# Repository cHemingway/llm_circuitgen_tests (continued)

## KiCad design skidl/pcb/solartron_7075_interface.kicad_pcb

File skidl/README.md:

# Solartron 7075 → USB interface (SKiDL)

An isolated USB interface for the Solartron 7075 DVM, described in
[SKiDL](https://github.com/devbisme/skidl) and laid out for KiCad 10. It plugs
into the 50-way Cannon socket (**SKB**) of the 7075's Parallel BCD Interface
Unit 70754 (service manual section 9). From there it reads the display data and
status lines, drives all the remote-control inputs, and connects to a host over
USB through an RP2354A.

| | |
|---|---|
| Board | 112 × 44 mm, 4 layers, 1.6 mm, rectangular, no mounting holes |
| Meter connector | J1, DD-50 **male** (plug), vertical, mounted on the **bottom** side. Two 4-40 jackscrews through its flange holes hold the board on the instrument |
| Host connector | J2, USB-B **vertical** (TE 5787834-1), mounted on the **top** side at the other end of the board |
| MCU | RP2354A (RP2350 with 2 MB of flash in the package), 12 MHz crystal, SWD header, BOOTSEL and RESET buttons |
| Isolation | 5 × TLP2361 optocouplers (4 to the meter, 1 back) + B0509S isolated DC/DC. There is a 4 mm copper-free gap between the domains (0.8 mm at the DC/DC pins) |
| Meter side | 5 × 74HCT165 (36 inputs + 4 check bits), 2 × 74HC595 (13 command outputs), supplied from its own regulated 5 V |
| Checks | SKiDL ERC: 0 errors / 0 warnings. Schematic ERC (KiCad 10, all severities): 0 violations (`pcb/erc_report.txt`). DRC with schematic parity (all severities): **0 violations, 0 unconnected, 0 parity errors** (`pcb/drc_report.txt`) |

## Schematic

One A2 sheet (`pcb/solartron_7075_interface.kicad_sch`, PDF in
`pcb/render/schematic.pdf`), grouped by function: USB input and 3.3 V, the
RP2354A, the isolation barrier (drawn as a dashed line through the
optocouplers and the DC/DC), the 595 command outputs, the meter-side 5 V, J1,
and the 165 input chain along the bottom. Labels with the same name are
connected.

SKiDL's own schematic output is not usable on this design (see
[Tool issues](#tool-issues)), so `scripts/gen_schematic.py` draws the sheet from
the SKiDL netlist. Part positions are set by hand per block; every pin then
gets a stub with a net label, power symbol or no-connect flag. The script
re-exports the netlist from the drawn sheet with `kicad-cli` and fails unless
every net has the same pins and the same name as in the SKiDL netlist.
`scripts/link_schematic.py` then ties the board's footprints to the symbols,
so KiCad's schematic-parity DRC and cross-probing work.

## How it works

```mermaid
flowchart LR
  subgraph USB["USB / host side (GND)"]
    J2[USB-B vertical] --> F1[500 mA PTC] --> ESD[USBLC6] --> LDO[AP2112K 3.3 V]
    LDO --> MCU[RP2354A]
    J2 -- D+/D- 27R --> MCU
  end
  subgraph ISO["Meter side (ISO_GND = 7075 pin 37 earth)"]
    REG[78L05] --> SR165[5 × 74HCT165]
    REG --> SR595[2 × 74HC595]
    SR595 --> Q1[2N7002 contact sample]
    SR165 --- RN[9 × 4 × 10k series]
  end
  MCU -- "SCLK, MOSI, LATCH, /OE (4 × TLP2361)" --> SR165 & SR595
  SR165 -- "MISO (1 × TLP2361)" --> MCU
  LDO -. "+5 V" .-> DCDC[B0509S 1 W isolated] -. "9 V" .-> REG
  RN --- J1[DD-50 plug to SKB]
  SR595 --- J1
  Q1 --- J1
```

* **Five signals cross the barrier.** SCLK, MOSI, LATCH and /OE go to the
  meter, and MISO comes back. Every meter output is captured by the 165 chain,
  and every meter input is driven by the 595 chain.
* **One LATCH line serves both chains.** LATCH low makes the 74HCT165s load
  (snapshot) the meter outputs. The rising edge of LATCH copies the 74HC595
  shift registers to their outputs.
* **The command outputs are safe at power-up.** The /OE optocoupler output sits
  high whenever its LED is off (MCU unpowered, in reset, or not yet
  initialised), so the 595 outputs stay high-impedance. The meter's TTL inputs
  then float to '1', which is the "nothing commanded" state. The manual notes
  that an unconnected interface leaves the meter in 10 s / DC V. The
  CONTACT-SAMPLE MOSFET has a 100 k gate pull-down for the same reason.
* **Logic levels follow the section-9 spec.**
  * Meter outputs are '1' = 2.4…6 V from a 6 kΩ source, so the 165s are
    **HCT** parts with TTL thresholds (V<sub>IH</sub> 2.0 V).
  * Each meter output passes through a 10 kΩ series resistor in a 4-way array.
    This limits ESD current and back-feeding when only one side is powered.
  * Meter inputs need '0' < 0.5 V at 5 mA sink and '1' < +5 V. The 74HC595
    meets both on a regulated 5 V.
  * That is why the meter side uses B0509S → 78L05 rather than an unregulated
    5 V → 5 V module. Such a module only holds 5 V above about 10 % load
    (20 mA), and this board draws about 15 mA, so its output would drift
    above the meter's input limit.
* **CONTACT SAMPLE** (pin 39) wants a real closure to pin 37, so it gets a
  2N7002. **PULSE SAMPLE** (pin 40) is driven directly (+5 V, keep it high for
  more than 100 µs).
* **Optocouplers.** The TLP2361 is a 15 MBd part with a totem-pole output and a
  threshold of ≤ 1.6 mA, so logic can drive its LED directly.
  * MCU side: 390 Ω from 3.3 V gives ≈ 3.6 mA.
  * Meter side: 820 Ω from 5 V gives ≈ 3.9 mA.
  * The LED cathode is pulled low by the driving logic, so each channel is
    non-inverting overall.

### RP2354A pin use

| GPIO | Pin | Function |
|---|---|---|
| GPIO20 | 32 | MISO (SPI0 RX) ← U9 |
| GPIO21 | 33 | LATCH → U7 |
| GPIO22 | 34 | SCLK (SPI0 SCK) → U5 |
| GPIO23 | 35 | MOSI (SPI0 TX) → U6 |
| GPIO24 | 36 | /OE of the 595s → U8 (drive low only after the first valid transfer) |
| GPIO5 | 8 | status LED D2 (active high) |
| SWCLK/SWDIO | 24/25 | J3 (SWCLK, GND, SWDIO) |
| QSPI_SS | 60 | BOOTSEL button SW1 (1 k) |
| RUN | 26 | RESET button SW2, 10 k pull-up |

GPIO20–24 are contiguous, so a single PIO program can drive them as well as
hardware SPI0. The QSPI pins are unconnected because the flash is inside the
RP2354A package.

## Transfer protocol and bit maps

Each transfer is 40 clocks: SPI mode 0, MSB first, SCLK ≤ 1 MHz recommended.
The optocouplers add about 0.2 µs round trip, which leaves plenty of margin
up to about 2 MHz.

1. Pulse LATCH low for ≥ 1 µs, then return it high. The pulse snapshots the
   meter outputs into the 165s. Its rising edge applies the command bytes sent
   in the previous transfer.
2. Clock 5 bytes. Read bytes 0–4 from MISO and send the command bytes on MOSI.
   Only the last two bytes sent stay in the 595 chain.
3. To apply new commands immediately, pulse LATCH again.

**MISO, bytes 0–4 (MSB first):**

| Byte | Register | bit7 … bit0 |
|---|---|---|
| 0 | U10 | 2 × 10² (16), PRINT PULSE (33), RANGE 1 (32), 1 × 10² (17), 2 × 10³ (12), RANGE 4 (30), 4 × 10² (15), 8 × 10² (14) |
| 1 | U11 | FUNC B (29), POL− (27), RANGE 2 (31), FUNC A (28), 1 × 10⁴ (9), 4 × 10³ (11), POL+ (26), 8 × 10³ (10) |
| 2 | U12 | 4 × 10⁴ (7), 2 × 10⁴ (8), 4 × 10⁰ (23), 1 × 10⁰ (25), DATA CAN CHANGE (35), 8 × 10⁴ (6), 8 × 10⁰ (22), 1 × 10¹ (21) |
| 3 | U13 | 4 × 10⁵ (3), 2 × 10¹ (20), 2 × 10⁵ (4), 4 × 10¹ (19), PRINT LEVEL (34), 8 × 10⁵ (2), 8 × 10¹ (18), 1 × 10⁶ (1) |
| 4 | U14 | 1 × 10⁵ (5), 1 × 10³ (13), OVERLOAD (36), 2 × 10⁰ (24), **1**, **0**, **1**, **0** |

Bits 3–0 of byte 4 are wired to a fixed `1010` pattern on the meter side.
If they read back as anything else, the link is broken or the isolated side is
unpowered: an unpowered side reads as all ones.

The bits don't follow the connector order, and a decade's four bits can be
split across registers. Each signal uses whichever array channel and register
input is nearest its connector pin (see [Routing review](#routing-review)).
Firmware should decode them with these tables, which are also printed on the
schematic.

**MOSI, bytes 3 and 4 (the last two sent):**

| Byte | Register | bit7 (QH) … bit0 (QA) |
|---|---|---|
| 3 | U16 | –, –, FRONT PANEL LOCKOUT (38, 0 = lockout/remote), FUNC (43), PULSE SAMPLE (40), FUNC (42), RATIO (41, 0 = ratio), CONTACT SAMPLE (39, via Q1, 1 = close) |
| 4 | U15 | REMOTE LED D4, RANGE 4 (50), RANGE 2 (49), RANGE 1 (48), INTEG 2 (45), AUTORANGE inhibit (47), INTEG 1 (46), INTEG 4 (44) |

Bytes 0–2 on MOSI are don't-care: they fall out of the end of the 595 chain.

Typical remote measurement:

1. Write the function, range and integration codes from the manual's tables,
   with LOCKOUT = 0.
2. Set PULSE SAMPLE = 1, wait ≥ 100 µs, then set it back to 0. Each change
   is one transfer plus a LATCH pulse.
3. Poll until PRINT LEVEL = 1.
4. Read the BCD digits, polarity, range and function codes from the same
   snapshot.

## Connector pin map (J1 ↔ 70754 SKB)

| SKB pin | Signal | Board net | SKB pin | Signal | Board net |
|---|---|---|---|---|---|
| 1 | 1 × 10⁶ | BCD_1E6_1 | 26 / 27 | +ve / −ve polarity | POL_POS / POL_NEG |
| 2–5 | 8,4,2,1 × 10⁵ | BCD_1E5_* | 28 / 29 | function out | FUNC_OUT_A / B |
| 6–9 | × 10⁴ | BCD_1E4_* | 30 / 31 / 32 | range out (4/2/1) | RANGE_OUT_* |
| 10–13 | × 10³ | BCD_1E3_* | 33 / 34 | print pulse / level | PRINT_PULSE / PRINT_LEVEL |
| 14–17 | × 10² | BCD_1E2_* | 35 / 36 | data can change / overload | DATA_CAN_CHANGE / OVERLOAD |
| 18–21 | × 10¹ | BCD_1E1_* | 37 | earth / logic 0 | **ISO_GND** (+ J1 shell) |
| 22–25 | × 10⁰ | BCD_1E0_* | 38–50 | command inputs | see MOSI map |

## Mechanical notes

* **J1 is on the underside**, centred at (36, 22) mm in the KiCad top view.
  * Its pins 1–17 (the wide row of the D) face the board's lower edge, the edge
    with the "ISOLATED (METER EARTH)" legend.
  * The jackscrew holes are Ø 3.2 mm at (5.445, 22) and (66.555, 22), 61.11 mm
    apart (DD-50 standard).
  * Fit two 4-40 UNC jackscrews or thumbscrews from the top through the board
    and the connector flange into the socket's screw-locks. Thread length should
    be ≥ 10 mm (1.6 mm board + flange + engagement).
  * No other parts sit on the underside. Keep at least 3 mm of clearance around
    the screw heads on top, which the layout already does.
* The board stands off the instrument by roughly the connector's body height,
  about 12 mm for the Amphenol Delta-D straight series. Check this against the
  part you buy.
* Relative to the socket, the board extends 36 mm on the J1 side and 76 mm on
  the USB side. If something on your unit is in the way on that side, J1's
  orientation can be changed in `scripts/layout_pcb.py` (`j1_ok`). Everything
  else then needs re-placing.
* The vertical USB-B on the top face points away from the instrument.

## Parts and sourcing

* Every part has an LCSC code. The grouped BOM with MPNs is in
  `output/bom.csv`, and the JLCPCB-format BOM and CPL are in `pcb/fab/`.
* Symbols and footprints come from the stock KiCad 10 libraries, except:
  * **J1:** KiCad 10 has no 50-way D-sub. `scripts/gen_dd50_footprint.py` and
    `scripts/gen_symbols.py` generate `lib/Solartron7075.*` from the Amphenol
    Delta-D drawing.
  * **TLP2361:** there is no KiCad symbol, so the identically-pinned
    `Isolator:TLP2310` symbol is used (SO6 with 5 leads: A 1, K 3, GND 4, VO 5,
    VCC 6). The footprint is `Toshiba_SOIC-5-6`.
  * **B0509S-1WR3:** uses the Murata MEE1 symbol and footprint, which have the
    same SIP-4 pinout.
* **J1 (Amphenol D50P24A4PA00LF, C17502305)** was listed on LCSC without stock
  at design time. Any straight-PCB DD-50 plug with plain 3.1 mm flange holes on
  the standard 2.77 × 2.84 mm grid fits. Don't use one with female screw-locks.
* The jackscrews are not on LCSC.
* Power budget is under 120 mA from USB:
  * RP2354A: ~30 mA
  * Opto LEDs: ≤ 15 mA
  * LEDs: ~5 mA
  * Isolated side: ≈ 15 mA at 5 V, ≈ 40 mA at the DC/DC input
* Isolation is **functional**: its purpose is to break the USB/earth ground loop
  and keep USB noise away from the meter. It is not a safety barrier. The
  TLP2361s are rated 3.75 kV<sub>rms</sub> and the B0509S 1.5 kV DC.

## Routing review

After review, the meter-side wiring was tidied in two rounds. J1, the
resistor arrays, the optocouplers and everything on the host side stayed
where they were.

1. **Pin swaps within parts** (`scripts/optimise_pins.py`). Every signal
   stayed on its original register and array. Only the pin it used there
   changed: the 74HCT165 D inputs, the array channels and the 74HC595
   outputs.
2. **Pin swaps between parts, and moved registers**
   (`scripts/optimise_layout.py`):
   * Any meter output may now use any array channel and any 74HCT165 input,
     so each signal takes the one nearest its connector pin. The four spare
     inputs become the link-check bits.
   * Any command input may use any 74HC595 output.
   * All seven registers are turned 180°, so their clock, latch and supply
     pins face away from J1 and the arrays. Their decoupling capacitors moved
     with the supply pins.
   * The 74HCT165s are reordered along the bottom row into chain order (U13,
     U12, U11, U10 from left to right), which puts U10 next to the MISO
     optocoupler. U15 and U16 swapped places.

Both scripts read the pad positions from the board. They use simulated
annealing to minimise the crossings of the straight pad-to-pad lines, plus
their length. The second round also counts the clock, latch, /OE, MOSI and
chain nets, so moving a register is weighed against its control wiring. The
result is in the `ARRAYS`, `REGS_165` and `REGS_595` tables in
`solartron_7075_interface.py` and the `BOTTOM_ROW` and `TOP_ROW` tables in
`scripts/layout_pcb.py`. Each round was re-routed with Freerouting.
`scripts/routing_metrics.py` measures the boards (original → round 1 → round
2):

| Nets | Straight-line crossings | Track length (mm) | Vias |
|---|---|---|---|
| J1 → resistor arrays (36) | 148 → 102 → **10** | 513 → 481 → **255** | 21 → 18 → **6** |
| Resistor arrays → 74HCT165s (36) | 64 → 0 → **0** | 441 → 351 → **372** | 72 → 70 → **72** |
| 74HC595s → J1 (13) | 36 → 8 → **1** | 265 → 205 → **137** | 11 → 11 → **7** |
| Clock, latch, /OE, MOSI, chains (10) | | 563 → 558 → **494** | 16 → 21 → **20** |
| Whole board | | 2428 → 2227 → **1868** | 262 → 260 → **243** |

DRC, ERC and the schematic-parity check are clean after each round.

The array-to-register links still drop to the bottom layer, at two vias
each, because of the 74HCT165 pinout. Its D inputs are rows 3–6 of each pin
column, behind Q7, DS, GND and ~Q7. Reaching them from above on the top layer
would need eight tracks between the pin columns, and they don't fit. On the
bottom layer the links are short, straight and parallel.

## Gerbers and prints

| File | Contents |
|---|---|
| `pcb/fab/gerbers.zip` | Gerbers for 4 layers, mask, paste, silkscreen and outline, plus Excellon drill files (PTH; the NPTH file is empty) and drill maps. Upload this to the board house |
| `pcb/fab/bom_jlcpcb.csv`, `pcb/fab/cpl_jlcpcb.csv` | JLCPCB assembly BOM and placement |
| `pcb/print/pcb_prints.pdf` | 7 A4 pages, black and white, with title block: top and bottom assembly (fab layers, pads sketched), F.Cu, In1.Cu, In2.Cu and B.Cu, all at 2:1, then a 1:1 bottom view for a fit check |
| `pcb/print/gerber_preview.png` | the Gerber and drill files rendered by gerbv, independently of KiCad |
| `pcb/render/` | KiCad 3D renders and a colour multi-layer PDF |

For the fit check, print page 7 at 100 % ("actual size"). The board outline
there should measure 112 × 44 mm. Hold it against the meter's SKB socket to
check the jackscrew holes, the pin rows and the overhang on each side. Bottom
views (pages 2, 6 and 7) are mirrored, so they show the board as seen from
the meter side.

## Files

| Path | What |
|---|---|
| `solartron_7075_interface.py` | the SKiDL design (all parts, nets, LCSC/MPN fields) |
| `lib/` | generated DD-50 symbol + footprint |
| `scripts/gen_dd50_footprint.py`, `scripts/gen_symbols.py` | library generators |
| `scripts/layout_pcb.py` | placement, stack-up, rules, planes, isolation keep-outs, silkscreen |
| `scripts/route_pcb.py`, `scripts/fanout.py` | QFN hand fan-out, plane vias, Freerouting, clean-up, ground pours |
| `scripts/gen_schematic.py` | draws the single-page schematic from the netlist and checks it (`--check`) |
| `scripts/link_schematic.py` | links the routed board to the schematic (symbol paths, net names) |
| `scripts/make_bom.py`, `scripts/jlc_cpl.py` | BOM and placement files |
| `scripts/optimise_pins.py`, `scripts/optimise_layout.py`, `scripts/routing_metrics.py` | meter-side pin-swap and register-placement searches, and the routing figures used to compare boards |
| `scripts/make_prints.py` | the print PDF and the Gerber preview |
| `build.sh` | runs the whole flow |
| `CONVERSATION.md` | export of the Claude Code session that produced this design, with its time and token totals |
| `REVIEW_CONVERSATION.md` | the review part of the same session (pin swaps and moved registers), with its statistics |
| `scripts/session_breakdown.py`, `stats/breakdown_calls.csv` | the split of the design session's statistics by kind of work, and the category of every API call |
| `scripts/review_breakdown.py`, `stats/review_breakdown_calls.csv` | the same for the review |
| `output/` | SKiDL netlist, ERC log, BOM, unplaced board straight from SKiDL |
| `pcb/` | KiCad 10 project: schematic, routed board, ERC and DRC reports, `render/` (schematic PDF/PNG, board renders), `print/` (prints, Gerber preview), `fab/` (Gerbers, drill, BOM, CPL) |

## Rebuilding

Tested with KiCad 10.0.6 (Ubuntu PPA), SKiDL 2.3.0 with kinet2pcb 1.1.4,
Freerouting 2.5.0 (needs Java 25), and Python 3.12. Use the system Python,
because it has KiCad's `pcbnew` module. The prints need `pdfunite` and
`pdftoppm` (poppler-utils) and ImageMagick. `gerbv` is optional; without it the
Gerber preview is skipped.

```sh
python3 -m venv --system-site-packages .venv && .venv/bin/pip install skidl
SKIDL_PYTHON=.venv/bin/python FREEROUTING_JAR=/path/freerouting-2.5.0-executable.jar \
JAVA=/usr/lib/jvm/java-25-openjdk-amd64/bin/java ./build.sh
```

The full run takes about 8 minutes, mostly in Freerouting's optimiser.
Freerouting is not fully deterministic, so a rebuild gives a board that is
equivalent but not byte-identical. The committed board is the one checked by
`pcb/drc_report.txt`.

## Session statistics breakdown

The root README's Breakdown table for SKiDL comes from
`scripts/session_breakdown.py`, which reads the session's Claude Code
transcript. The category of each of the 347 API calls is listed in
`stats/breakdown_calls.csv`. Notes on the method:

* **Span.** The span runs from the first prompt to the request to export the
  conversation, the same as the Results row. This session has not had the
  review comments yet.
* **Categories.** Calls are assigned by hand, from index ranges in the script.
  The less obvious calls:
  * Installing KiCad and SKiDL counts as tool research. Freerouting, Java and
    the 3D models count as PCB.
  * Checking which footprints fit the chosen parts counts as PCB, and so does
    the DD-50 footprint.
  * The BOM and the later LED and passive swaps count as part selection.
  * Linking the board to the schematic (`link_schematic.py`, the parity DRC)
    counts as PCB.
* **Cache rewrite.** "Other" includes a 0.62 M-token prompt-cache write
  (about $5). The first call after the 6 h pause at the usage limit had to
  re-cache the whole conversation, and that call was a `git status` check.
* **Not attributable.** This column holds the automatic compaction (77 s) and
  1.13 M tokens that the cost counter includes but the transcript does not log
  per call.
* **Prices.** The fitted prices are $4.41 per million input tokens, $8.00 for
  cache writes, $0.200 for cache reads and $20.03 for output.
  * They reproduce all four of the session's cost snapshots to within 1e-13
    dollars.
  * Four snapshots and four prices make the fit exact. So it is checked only
    by the other three prices coming out as round figures.
  * The input price is poorly determined, because there are only 5 k uncached
    input tokens. Its effect on any column is under $0.02.
  * Snapshots written later in the session (nine in all) refit the input price
    to $3.90. Re-running the script then gives $7.52 for "Other" instead of
    the published $7.51.

## Tool issues

Problems with SKiDL, kinet2pcb, Freerouting and the KiCad libraries, and what
this flow does about them.

* **SKiDL schematic generator.** SKiDL 2.3's KiCad 10 schematic output
  (`SKIDL_SCH=1`, hierarchical or flat) runs, but on this design it draws some
  power symbols and labels touching other nets. KiCad's netlist export of the
  result merges nets, e.g. +3V3 with +1V1_DVDD, and puts decoupling caps on the
  wrong rails. It is off by default. The shipped sheet comes from
  `scripts/gen_schematic.py` and is checked against the netlist, as described
  under [Schematic](#schematic).
* **kinet2pcb:**
  * It can't parse KiCad 10's quoted `fp-lib-table` entries, so the footprint
    directories are passed explicitly.
  * It puts every no-connect pin on one shared `__NOCONNECT` net, so
    `layout_pcb.py` detaches them.
  * Its footprints carry no symbol paths, so the board is not linked to any
    schematic. `link_schematic.py` adds the paths and BOM fields, renames nets
    the way KiCad's "Update PCB from Schematic" would (local-label nets become
    `/NAME`), and gives no-connect pins their `unconnected-(…)` nets.
* **SKiDL pin names.** SKiDL mangles pin names containing `'` (the 595's
  `QH'`), so pin numbers are used there.
* **Freerouting** doesn't drop vias into the inner planes by itself, and it
  can't escape the RP2354A's 0.4 mm-pitch supply pins. The QFN fan-out and the
  plane vias are pre-routed and locked, and Freerouting routes the rest. It is
  also not fully deterministic (see [Rebuilding](#rebuilding)).
* **KiCad libraries.** There is no 50-way D-sub footprint or TLP2361 symbol,
  so these are generated or substituted (see
  [Parts and sourcing](#parts-and-sourcing)). The 3D library has no models for
  the DD-50, the vertical USB-B, the TS-1187A switches, the MEE1/B0509S or the
  QFN-60, so those parts are missing from the renders.

## Design caveats

* **Not built or bench-tested.** Before ordering:
  * Check J1's footprint against the datasheet of the plug you actually buy.
  * Check the jackscrew thread and the socket orientation on your 70754.
  * Check the orientation of every part in JLCPCB's placement preview.
* **Power sequencing.** If the meter is switched off while the board is powered
  and /OE is enabled, the 595 outputs back-feed the meter's TTL inputs.
  Firmware should release /OE when the meter outputs read implausibly, for
  example everything low.
* The 595s' '1' level is the 78L05 output, 5.0 V ± 4 %. The manual gives
  "< +5 V" for its inputs, which the TTL inputs tolerate.
* J1 had no LCSC stock at design time, and the jackscrews are not on LCSC (see
  [Parts and sourcing](#parts-and-sourcing)).
* Isolation is functional, not a safety barrier.
* No firmware is included.

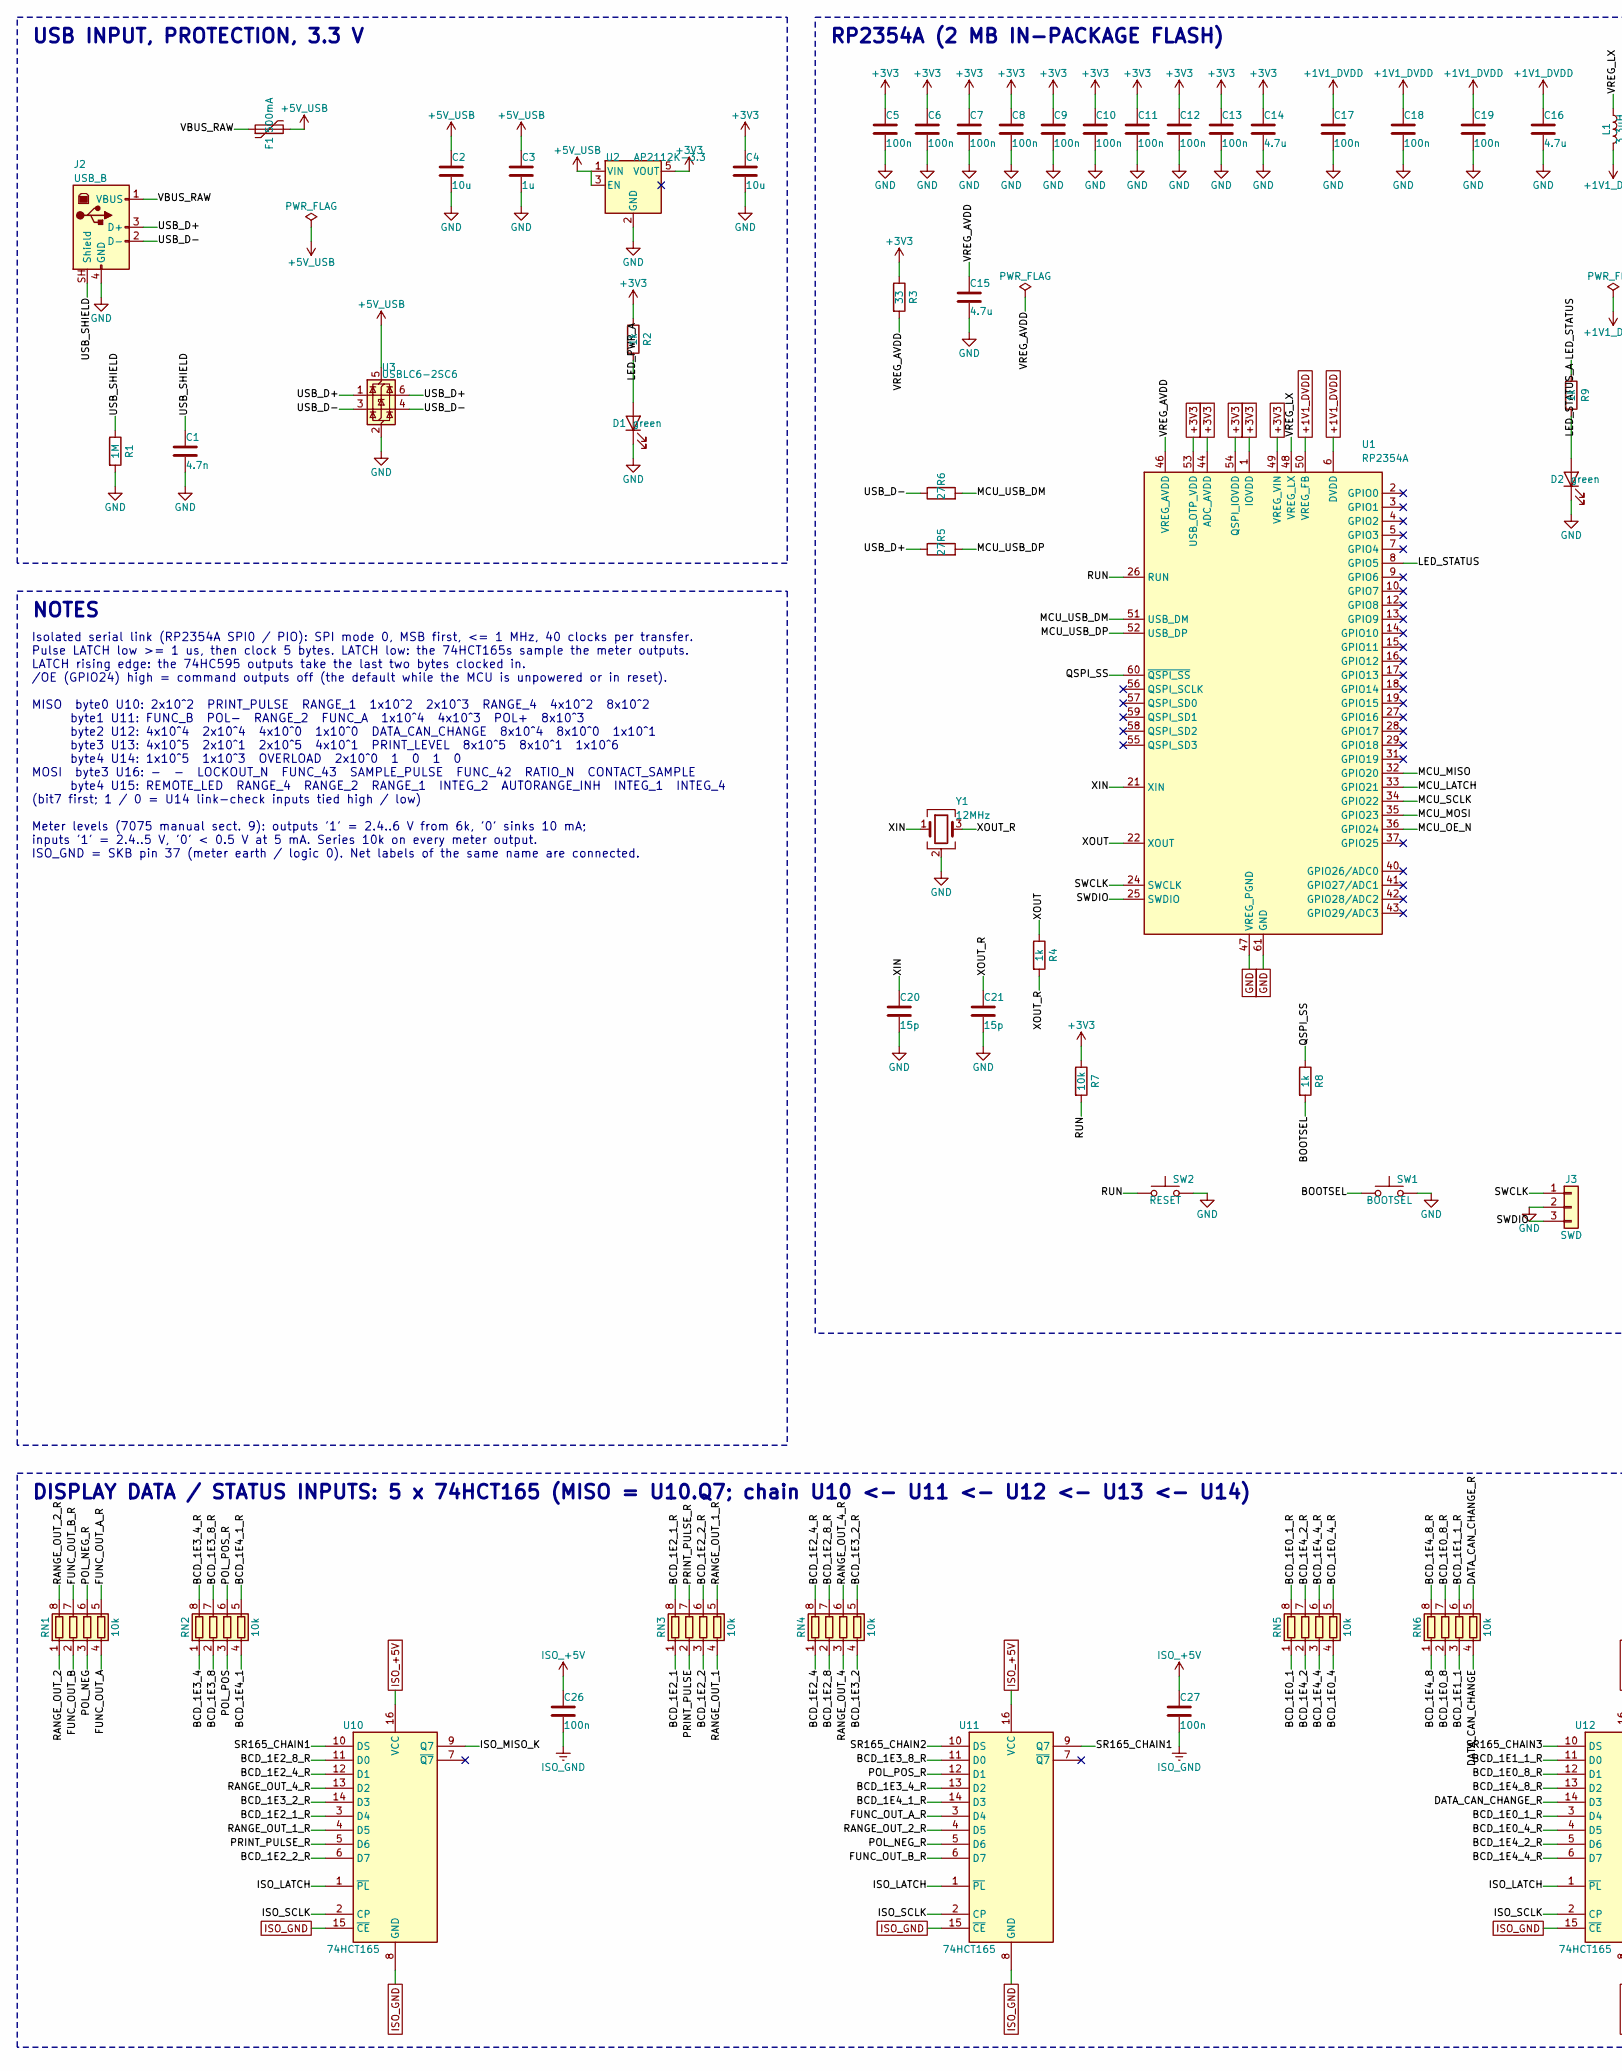
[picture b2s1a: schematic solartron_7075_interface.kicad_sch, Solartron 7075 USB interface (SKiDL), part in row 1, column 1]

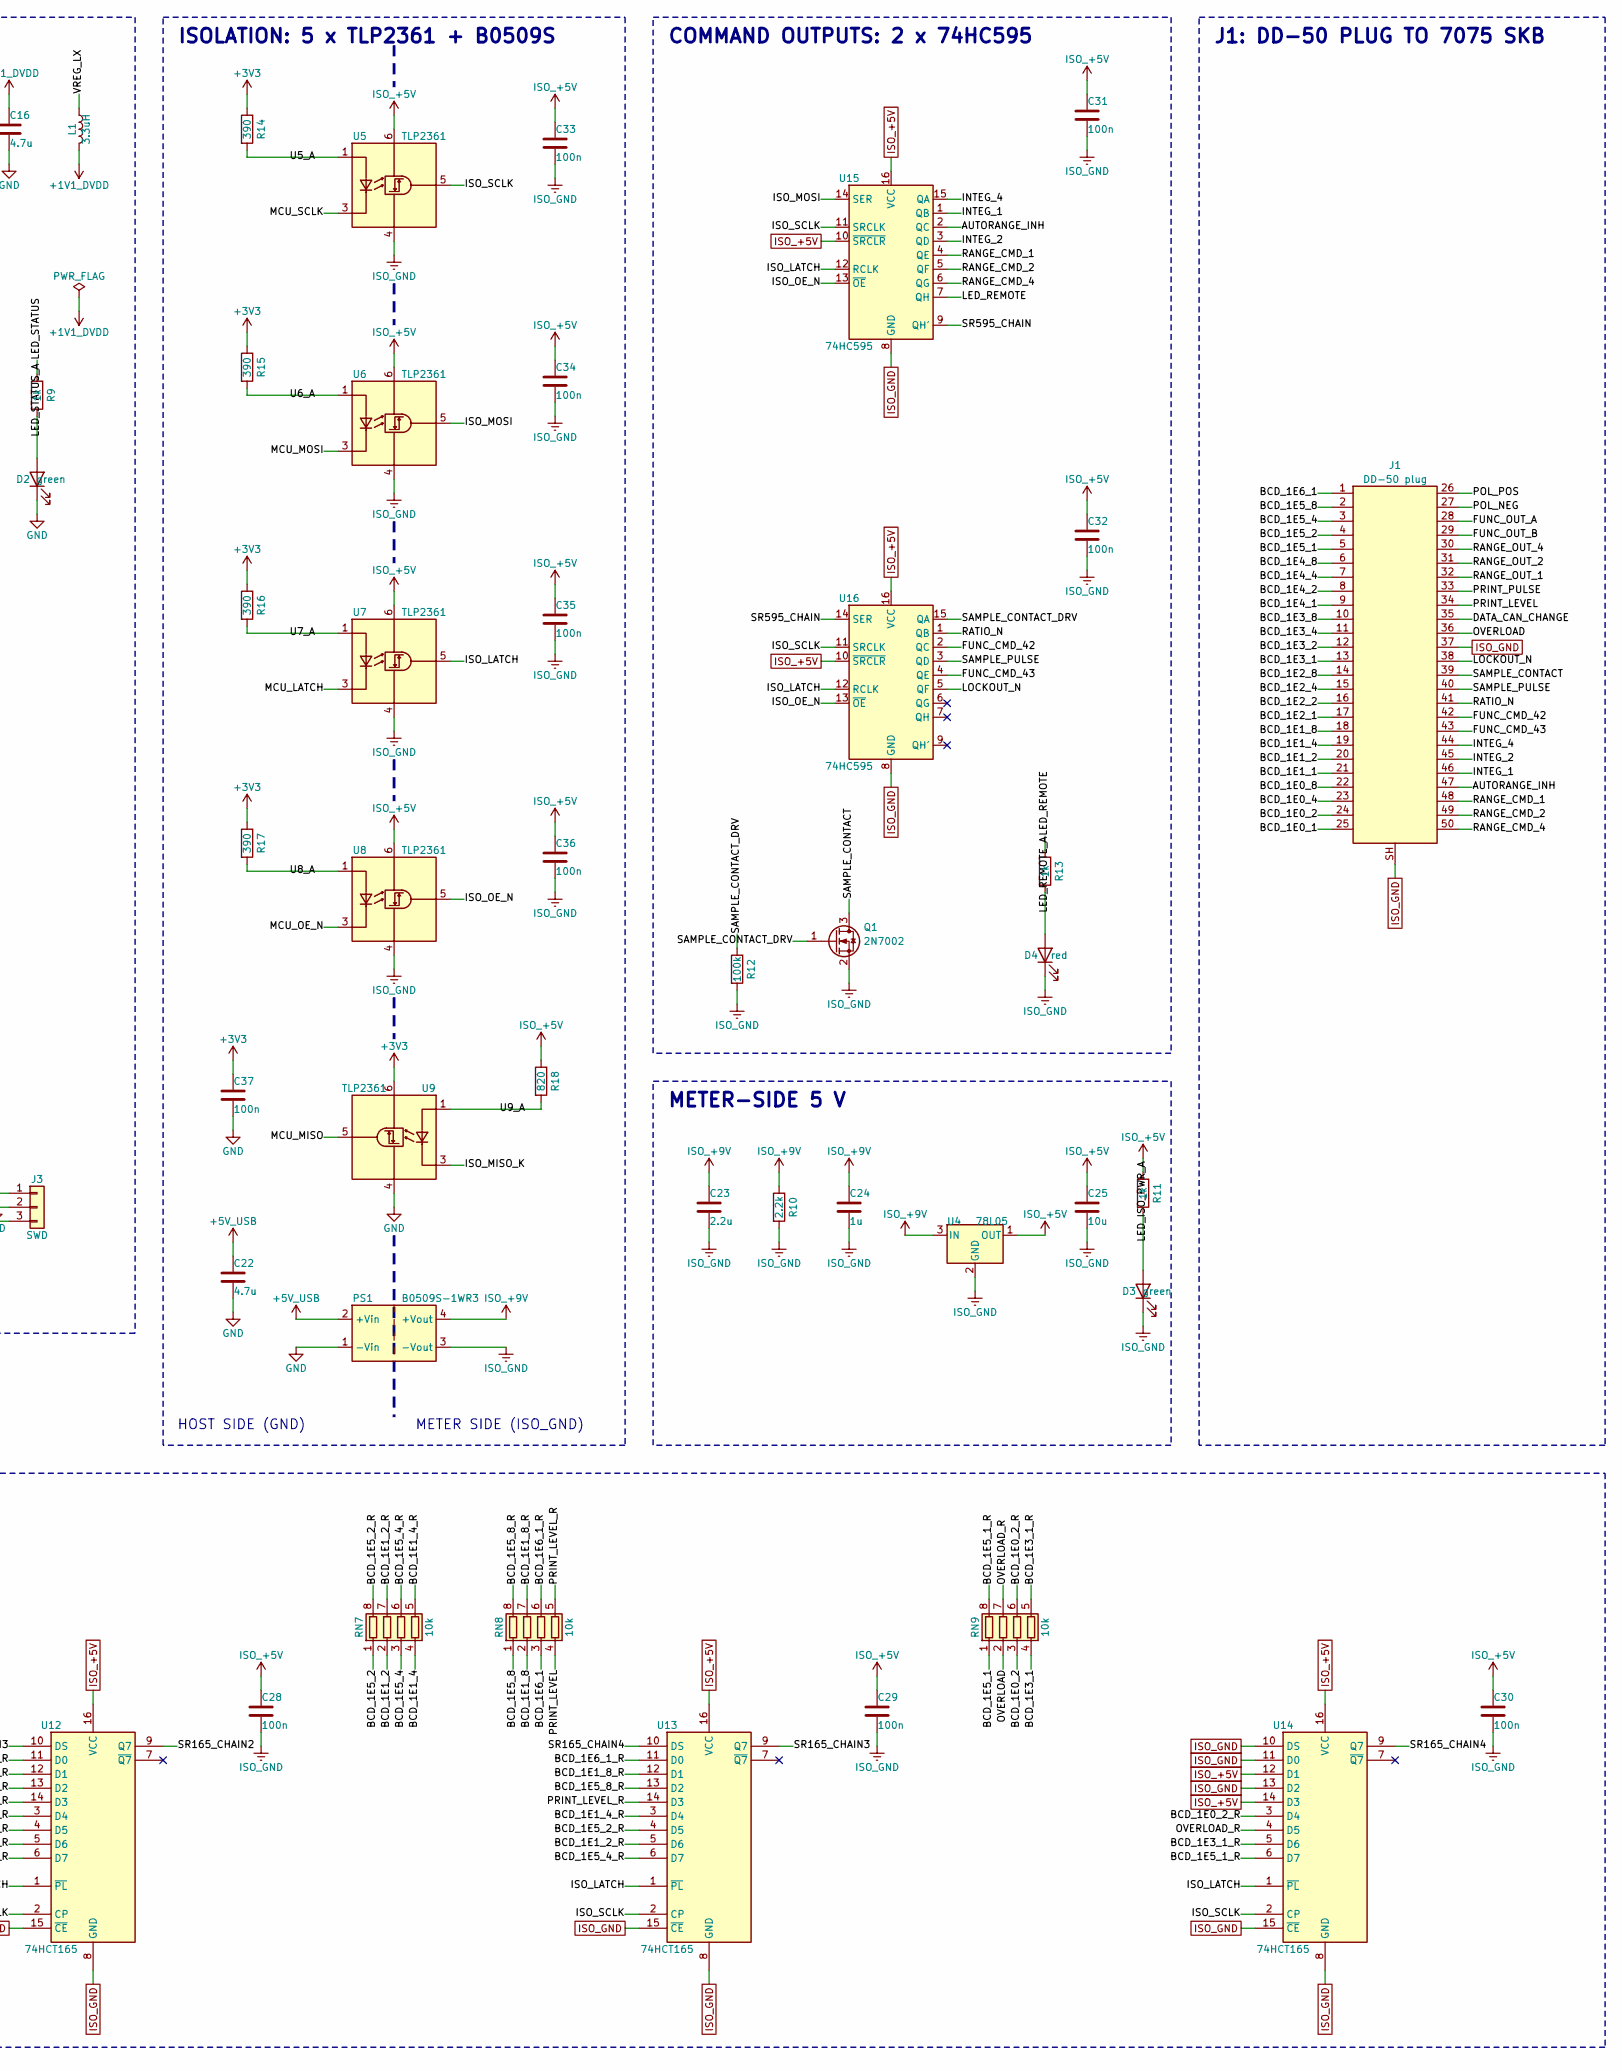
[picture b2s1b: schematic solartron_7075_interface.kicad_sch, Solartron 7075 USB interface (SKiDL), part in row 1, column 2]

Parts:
C1: 4.7n; C_0603_1608Metric; MPN 0603B472K500NT; LCSC C53987
C2, C4, C25: 10u; C_0603_1608Metric; MPN CL10A106KP8NNNC; LCSC C19702
C3, C24: 1u; C_0603_1608Metric; MPN CL10A105KB8NNNC; LCSC C15849
C5, C6, C7, C8, C9, C10, C11, C12, C13, C17, C18, C19: 100n; C_0402_1005Metric; MPN CL05B104KO5NNNC; LCSC C1525
C14, C15, C16: 4.7u; C_0402_1005Metric; MPN CL05A475MP5NRNC; LCSC C23733
C20, C21: 15p; C_0402_1005Metric; MPN 0402CG150J500NT; LCSC C1548
C22: 4.7u; C_0603_1608Metric; MPN CL10A475KO8NNNC; LCSC C19666
C23: 2.2u; C_0603_1608Metric; MPN CL10A225KO8NNNC; LCSC C23630
C26, C27, C28, C29, C30, C31, C32, C33, C34, C35, C36, C37: 100n; C_0603_1608Metric; MPN CC0603KRX7R9BB104; LCSC C14663
D1, D2, D3: green; LED_0603_1608Metric; MPN LTST-C190KGKT; LCSC C125094
D4: red; LED_0603_1608Metric; MPN KT-0603R; LCSC C2286
F1: 500mA; Fuse_1206_3216Metric; MPN SMD1206P050TF; LCSC C20799
J1: DD-50 plug; DSUB-50_Pins_Vertical_P2.77x2.84mm_MountingHoles; MPN D50P24A4PA00LF; LCSC C17502305
J2: USB_B; USB_B_TE_5787834_Vertical; MPN 5787834-1; LCSC C592900
J3: SWD; PinHeader_1x03_P2.54mm_Vertical; MPN PZ254V-11-03P; LCSC C2937625
L1: 3.3uH; L_Murata_DFE201610P; MPN AOTA-B201610S3R3-101-T; LCSC C42411119
PS1: B0509S-1WR3; Converter_DCDC_Murata_MEE1SxxxxSC_THT; MPN B0509S-1WR3; LCSC C7500906
Q1: 2N7002; SOT-23; MPN 2N7002; LCSC C8545
R1: 1M; R_0603_1608Metric; MPN 0603WAF1004T5E; LCSC C22935
R2, R11, R13: 1k; R_0603_1608Metric; MPN 0603WAF1001T5E; LCSC C21190
R3: 33; R_0402_1005Metric; MPN 0402WGF330JTCE; LCSC C25105
R4, R8, R9: 1k; R_0402_1005Metric; MPN 0402WGF1001TCE; LCSC C11702
R5, R6: 27; R_0402_1005Metric; MPN 0402WGF270JTCE; LCSC C25100
R7: 10k; R_0402_1005Metric; MPN 0402WGF1002TCE; LCSC C25744
R10: 2.2k; R_0603_1608Metric; MPN 0603WAF2201T5E; LCSC C4190
R12: 100k; R_0603_1608Metric; MPN 0603WAF1003T5E; LCSC C25803
R14, R15, R16, R17: 390; R_0603_1608Metric; MPN 0603WAF3900T5E; LCSC C23151
R18: 820; R_0603_1608Metric; MPN 0603WAF8200T5E; LCSC C23253
RN1, RN2, RN3, RN4, RN5, RN6, RN7, RN8, RN9: 10k; R_Array_Convex_4x0603; MPN 4D03WGJ0103T5E; LCSC C29718
SW1: BOOTSEL; SW_Push_1P1T_XKB_TS-1187A; MPN TS-1187A-B-A-B; LCSC C318884
SW2: RESET; SW_Push_1P1T_XKB_TS-1187A; MPN TS-1187A-B-A-B; LCSC C318884
U1: RP2354A; QFN-60-1EP_7x7mm_P0.4mm_EP3.4x3.4mm_ThermalVias; MPN RP2354A; LCSC C41378174
U2: AP2112K-3.3; SOT-23-5; MPN AP2112K-3.3TRG1; LCSC C51118
U3: USBLC6-2SC6; SOT-23-6; MPN USBLC6-2SC6; LCSC C7519
U4: 78L05; SOT-89-3; MPN 78L05 (SOT-89); LCSC C347258
U5, U6, U7, U8, U9: TLP2361; Toshiba_SOIC-5-6_4.4x3.6mm_P1.27mm; MPN TLP2361(TPL,E; LCSC C107626
U10, U11, U12, U13, U14: 74HCT165; SOIC-16_3.9x9.9mm_P1.27mm; MPN 74HCT165D,653; LCSC C456131
U15, U16: 74HC595; SOIC-16_3.9x9.9mm_P1.27mm; MPN 74HC595D,118; LCSC C5947
Y1: 12MHz; Crystal_SMD_3225-4Pin_3.2x2.5mm; MPN ABM8-272-T3; LCSC C20625731

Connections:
+1V1_DVDD: C16.1, C17.1, C18.1, C19.1, L1.2, U1.6 (DVDD), U1.23 (DVDD), U1.39 (DVDD), U1.50 (VREG_FB)
+3V3: C4.1, C5.1, C6.1, C7.1, C8.1, C9.1, C10.1, C11.1, C12.1, C13.1, C14.1, C37.1, R2.1, R3.1, R7.1, R14.1, R15.1, R16.1, R17.1, U1.1 (IOVDD), U1.11 (IOVDD), U1.20 (IOVDD), U1.30 (IOVDD), U1.38 (IOVDD), U1.44 (ADC_AVDD), U1.45 (IOVDD), U1.49 (VREG_VIN), U1.53 (USB_OTP_VDD), U1.54 (QSPI_IOVDD), U2.5 (VOUT), U9.6 (VDD)
+5V_USB: C2.1, C3.1, C22.1, F1.2, PS1.2 (+Vin), U2.1 (VIN), U2.3 (EN), U3.5 (VBUS)
/AUTORANGE_INH: J1.47, U15.2 (QC)
/BCD_1E0_1: J1.25, RN5.1 (R1.1)
/BCD_1E0_1_R: RN5.8 (R1.2), U12.3 (D4)
/BCD_1E0_2: J1.24, RN9.3 (R3.1)
/BCD_1E0_2_R: RN9.6 (R3.2), U14.3 (D4)
/BCD_1E0_4: J1.23, RN5.4 (R4.1)
/BCD_1E0_4_R: RN5.5 (R4.2), U12.4 (D5)
/BCD_1E0_8: J1.22, RN6.2 (R2.1)
/BCD_1E0_8_R: RN6.7 (R2.2), U12.12 (D1)
/BCD_1E1_1: J1.21, RN6.3 (R3.1)
/BCD_1E1_1_R: RN6.6 (R3.2), U12.11 (D0)
/BCD_1E1_2: J1.20, RN7.2 (R2.1)
/BCD_1E1_2_R: RN7.7 (R2.2), U13.5 (D6)
/BCD_1E1_4: J1.19, RN7.4 (R4.1)
/BCD_1E1_4_R: RN7.5 (R4.2), U13.3 (D4)
/BCD_1E1_8: J1.18, RN8.2 (R2.1)
/BCD_1E1_8_R: RN8.7 (R2.2), U13.12 (D1)
/BCD_1E2_1: J1.17, RN3.1 (R1.1)
/BCD_1E2_1_R: RN3.8 (R1.2), U10.3 (D4)
/BCD_1E2_2: J1.16, RN3.3 (R3.1)
/BCD_1E2_2_R: RN3.6 (R3.2), U10.6 (D7)
/BCD_1E2_4: J1.15, RN4.1 (R1.1)
/BCD_1E2_4_R: RN4.8 (R1.2), U10.12 (D1)
/BCD_1E2_8: J1.14, RN4.2 (R2.1)
/BCD_1E2_8_R: RN4.7 (R2.2), U10.11 (D0)
/BCD_1E3_1: J1.13, RN9.4 (R4.1)
/BCD_1E3_1_R: RN9.5 (R4.2), U14.5 (D6)
/BCD_1E3_2: J1.12, RN4.4 (R4.1)
/BCD_1E3_2_R: RN4.5 (R4.2), U10.14 (D3)
/BCD_1E3_4: J1.11, RN2.1 (R1.1)
/BCD_1E3_4_R: RN2.8 (R1.2), U11.13 (D2)
/BCD_1E3_8: J1.10, RN2.2 (R2.1)
/BCD_1E3_8_R: RN2.7 (R2.2), U11.11 (D0)
/BCD_1E4_1: J1.9, RN2.4 (R4.1)
/BCD_1E4_1_R: RN2.5 (R4.2), U11.14 (D3)
/BCD_1E4_2: J1.8, RN5.2 (R2.1)
/BCD_1E4_2_R: RN5.7 (R2.2), U12.5 (D6)
/BCD_1E4_4: J1.7, RN5.3 (R3.1)
/BCD_1E4_4_R: RN5.6 (R3.2), U12.6 (D7)
/BCD_1E4_8: J1.6, RN6.1 (R1.1)
/BCD_1E4_8_R: RN6.8 (R1.2), U12.13 (D2)
/BCD_1E5_1: J1.5, RN9.1 (R1.1)
/BCD_1E5_1_R: RN9.8 (R1.2), U14.6 (D7)
/BCD_1E5_2: J1.4, RN7.1 (R1.1)
/BCD_1E5_2_R: RN7.8 (R1.2), U13.4 (D5)
/BCD_1E5_4: J1.3, RN7.3 (R3.1)
/BCD_1E5_4_R: RN7.6 (R3.2), U13.6 (D7)
/BCD_1E5_8: J1.2, RN8.1 (R1.1)
/BCD_1E5_8_R: RN8.8 (R1.2), U13.13 (D2)
/BCD_1E6_1: J1.1, RN8.3 (R3.1)
/BCD_1E6_1_R: RN8.6 (R3.2), U13.11 (D0)
/BOOTSEL: R8.2, SW1.1
/DATA_CAN_CHANGE: J1.35, RN6.4 (R4.1)
/DATA_CAN_CHANGE_R: RN6.5 (R4.2), U12.14 (D3)
/FUNC_CMD_42: J1.42, U16.2 (QC)
/FUNC_CMD_43: J1.43, U16.4 (QE)
/FUNC_OUT_A: J1.28, RN1.4 (R4.1)
/FUNC_OUT_A_R: RN1.5 (R4.2), U11.3 (D4)
/FUNC_OUT_B: J1.29, RN1.2 (R2.1)
/FUNC_OUT_B_R: RN1.7 (R2.2), U11.6 (D7)
/INTEG_1: J1.46, U15.1 (QB)
/INTEG_2: J1.45, U15.3 (QD)
/INTEG_4: J1.44, U15.15 (QA)
/ISO_LATCH: U7.5 (VO), U10.1 (~PL), U11.1 (~PL), U12.1 (~PL), U13.1 (~PL), U14.1 (~PL), U15.12 (RCLK), U16.12 (RCLK)
/ISO_MISO_K: U9.3 (K), U10.9 (Q7)
/ISO_MOSI: U6.5 (VO), U15.14 (SER)
/ISO_OE_N: U8.5 (VO), U15.13 (~OE), U16.13 (~OE)
/ISO_SCLK: U5.5 (VO), U10.2 (CP), U11.2 (CP), U12.2 (CP), U13.2 (CP), U14.2 (CP), U15.11 (SRCLK), U16.11 (SRCLK)
/LED_ISO_PWR_A: D3.2 (A), R11.2
/LED_PWR_A: D1.2 (A), R2.2
/LED_REMOTE: R13.1, U15.7 (QH)
/LED_REMOTE_A: D4.2 (A), R13.2
/LED_STATUS: R9.1, U1.8 (GPIO5)
/LED_STATUS_A: D2.2 (A), R9.2
/LOCKOUT_N: J1.38, U16.5 (QF)
/MCU_LATCH: U1.33 (GPIO21), U7.3 (K)
/MCU_MISO: U1.32 (GPIO20), U9.5 (VO)
/MCU_MOSI: U1.35 (GPIO23), U6.3 (K)
/MCU_OE_N: U1.36 (GPIO24), U8.3 (K)
/MCU_SCLK: U1.34 (GPIO22), U5.3 (K)
/MCU_USB_DM: R6.2, U1.51 (USB_DM)
/MCU_USB_DP: R5.2, U1.52 (USB_DP)
/OVERLOAD: J1.36, RN9.2 (R2.1)
/OVERLOAD_R: RN9.7 (R2.2), U14.4 (D5)
/POL_NEG: J1.27, RN1.3 (R3.1)
/POL_NEG_R: RN1.6 (R3.2), U11.5 (D6)
/POL_POS: J1.26, RN2.3 (R3.1)
/POL_POS_R: RN2.6 (R3.2), U11.12 (D1)
/PRINT_LEVEL: J1.34, RN8.4 (R4.1)
/PRINT_LEVEL_R: RN8.5 (R4.2), U13.14 (D3)
/PRINT_PULSE: J1.33, RN3.2 (R2.1)
/PRINT_PULSE_R: RN3.7 (R2.2), U10.5 (D6)
/QSPI_SS: R8.1, U1.60 (~QSPI_SS)
/RANGE_CMD_1: J1.48, U15.4 (QE)
/RANGE_CMD_2: J1.49, U15.5 (QF)
/RANGE_CMD_4: J1.50, U15.6 (QG)
/RANGE_OUT_1: J1.32, RN3.4 (R4.1)
/RANGE_OUT_1_R: RN3.5 (R4.2), U10.4 (D5)
/RANGE_OUT_2: J1.31, RN1.1 (R1.1)
/RANGE_OUT_2_R: RN1.8 (R1.2), U11.4 (D5)
/RANGE_OUT_4: J1.30, RN4.3 (R3.1)
/RANGE_OUT_4_R: RN4.6 (R3.2), U10.13 (D2)
/RATIO_N: J1.41, U16.1 (QB)
/RUN: R7.2, SW2.1, U1.26 (RUN)
/SAMPLE_CONTACT: J1.39, Q1.3 (D)
/SAMPLE_CONTACT_DRV: Q1.1 (G), R12.1, U16.15 (QA)
/SAMPLE_PULSE: J1.40, U16.3 (QD)
/SR165_CHAIN1: U10.10 (DS), U11.9 (Q7)
/SR165_CHAIN2: U11.10 (DS), U12.9 (Q7)
/SR165_CHAIN3: U12.10 (DS), U13.9 (Q7)
/SR165_CHAIN4: U13.10 (DS), U14.9 (Q7)
/SR595_CHAIN: U15.9 (QH'), U16.14 (SER)
/SWCLK: J3.1, U1.24 (SWCLK)
/SWDIO: J3.3, U1.25 (SWDIO)
/U5_A: R14.2, U5.1 (A)
/U6_A: R15.2, U6.1 (A)
/U7_A: R16.2, U7.1 (A)
/U8_A: R17.2, U8.1 (A)
/U9_A: R18.2, U9.1 (A)
/USB_D+: J2.3 (D+), R5.1, U3.1 (I/O1), U3.6 (I/O1)
/USB_D-: J2.2 (D-), R6.1, U3.3 (I/O2), U3.4 (I/O2)
/USB_SHIELD: C1.1, J2.SH (Shield), R1.1
/VBUS_RAW: F1.1, J2.1 (VBUS)
/VREG_AVDD: C15.1, R3.2, U1.46 (VREG_AVDD)
/VREG_LX: L1.1, U1.48 (VREG_LX)
/XIN: C20.1, U1.21 (XIN), Y1.1
/XOUT: R4.1, U1.22 (XOUT)
/XOUT_R: C21.1, R4.2, Y1.3
GND: C1.2, C2.2, C3.2, C4.2, C5.2, C6.2, C7.2, C8.2, C9.2, C10.2, C11.2, C12.2, C13.2, C14.2, C15.2, C16.2, C17.2, C18.2, C19.2, C20.2, C21.2, C22.2, C37.2, D1.1 (K), D2.1 (K), J2.4 (GND), J3.2, PS1.1 (-Vin), R1.2, SW1.2, SW2.2, U1.47 (VREG_PGND), U1.61 (GND), U2.2 (GND), U3.2 (GND), U9.4 (GND), Y1.2 (G), Y1.4 (G)
ISO_+5V: C25.1, C26.1, C27.1, C28.1, C29.1, C30.1, C31.1, C32.1, C33.1, C34.1, C35.1, C36.1, R11.1, R18.1, U4.1 (OUT), U5.6 (VDD), U6.6 (VDD), U7.6 (VDD), U8.6 (VDD), U10.16 (VCC), U11.16 (VCC), U12.16 (VCC), U13.16 (VCC), U14.12 (D1), U14.14 (D3), U14.16 (VCC), U15.10 (~SRCLR), U15.16 (VCC), U16.10 (~SRCLR), U16.16 (VCC)
ISO_+9V: C23.1, C24.1, PS1.4 (+Vout), R10.1, U4.3 (IN)
ISO_GND: C23.2, C24.2, C25.2, C26.2, C27.2, C28.2, C29.2, C30.2, C31.2, C32.2, C33.2, C34.2, C35.2, C36.2, D3.1 (K), D4.1 (K), J1.37, J1.SH, PS1.3 (-Vout), Q1.2 (S), R10.2, R12.2, U4.2 (GND), U5.4 (GND), U6.4 (GND), U7.4 (GND), U8.4 (GND), U10.8 (GND), U10.15 (~CE), U11.8 (GND), U11.15 (~CE), U12.8 (GND), U12.15 (~CE), U13.8 (GND), U13.15 (~CE), U14.8 (GND), U14.10 (DS), U14.11 (D0), U14.13 (D2), U14.15 (~CE), U15.8 (GND), U16.8 (GND)

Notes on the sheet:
USB INPUT, PROTECTION, 3.3 V
NOTES
Isolated serial link (RP2354A SPI0 / PIO): SPI mode 0, MSB first, <= 1 MHz, 40 clocks per transfer. Pulse LATCH low >= 1 us, then clock 5 bytes. LATCH low: the 74HCT165s sample the meter outputs. LATCH rising edge: the 74HC595 outputs take the last two bytes clocked in. /OE (GPIO24) high = command 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
RP2354A (2 MB IN-PACKAGE FLASH)
ISOLATION: 5 x TLP2361 + B0509S
HOST SIDE (GND)
METER SIDE (ISO_GND)
METER-SIDE 5 V
COMMAND OUTPUTS: 2 x 74HC595
J1: DD-50 PLUG TO 7075 SKB
DISPLAY DATA / STATUS INPUTS: 5 x 74HCT165 (MISO = U10.Q7; chain U10 <- U11 <- U12 <- U13 <- U14)

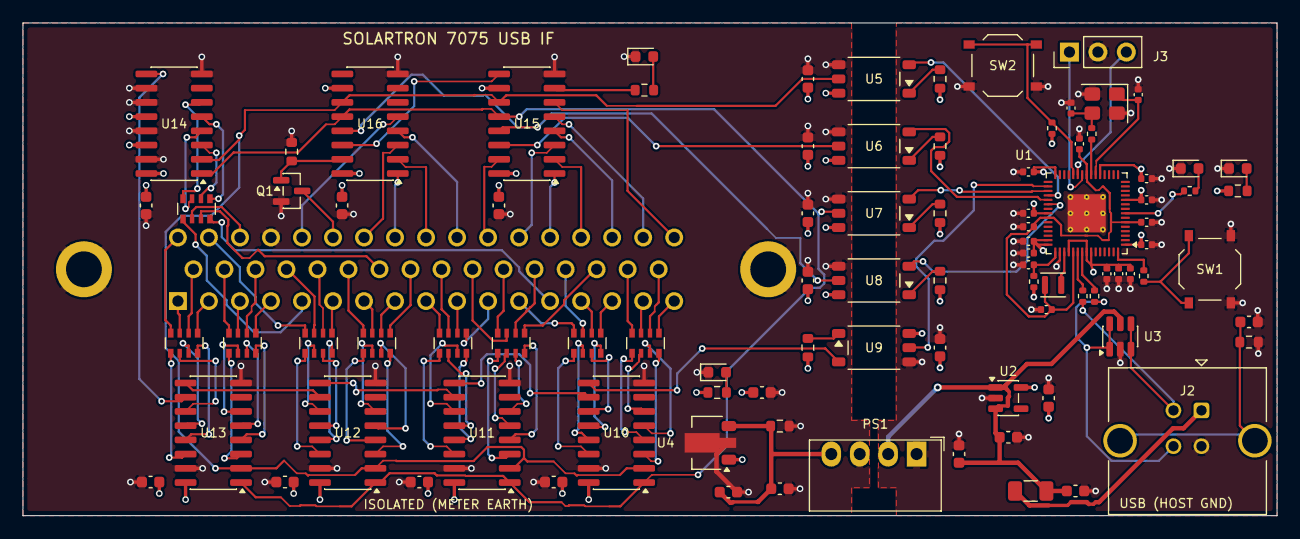
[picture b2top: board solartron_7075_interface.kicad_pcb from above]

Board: 4 copper layers, 112.0 x 44.0 mm, 94 parts (1 on the bottom side), 135 nets.

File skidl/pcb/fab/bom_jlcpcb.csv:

Comment,Designator,Footprint,LCSC Part #
4.7n,C1,C_0603_1608Metric,C53987
10u,"C2,C4,C25",C_0603_1608Metric,C19702
1u,"C3,C24",C_0603_1608Metric,C15849
100n,"C5,C6,C7,C8,C9,C10,C11,C12,C13,C17,C18,C19",C_0402_1005Metric,C1525
4.7u,"C14,C15,C16",C_0402_1005Metric,C23733
15p,"C20,C21",C_0402_1005Metric,C1548
4.7u,C22,C_0603_1608Metric,C19666
2.2u,C23,C_0603_1608Metric,C23630
100n,"C26,C27,C28,C29,C30,C31,C32,C33,C34,C35,C36,C37",C_0603_1608Metric,C14663
green,"D1,D2,D3",LED_0603_1608Metric,C125094
red,D4,LED_0603_1608Metric,C2286
500mA,F1,Fuse_1206_3216Metric,C20799
DD-50 plug,J1,DSUB-50_Pins_Vertical_P2.77x2.84mm_MountingHoles,C17502305
USB_B,J2,USB_B_TE_5787834_Vertical,C592900
SWD,J3,PinHeader_1x03_P2.54mm_Vertical,C2937625
3.3uH,L1,L_Murata_DFE201610P,C42411119
B0509S-1WR3,PS1,Converter_DCDC_Murata_MEE1SxxxxSC_THT,C7500906
2N7002,Q1,SOT-23,C8545
1M,R1,R_0603_1608Metric,C22935
1k,"R2,R11,R13",R_0603_1608Metric,C21190
33,R3,R_0402_1005Metric,C25105
1k,"R4,R8,R9",R_0402_1005Metric,C11702
27,"R5,R6",R_0402_1005Metric,C25100
10k,R7,R_0402_1005Metric,C25744
2.2k,R10,R_0603_1608Metric,C4190
100k,R12,R_0603_1608Metric,C25803
390,"R14,R15,R16,R17",R_0603_1608Metric,C23151
820,R18,R_0603_1608Metric,C23253
10k,"RN1,RN2,RN3,RN4,RN5,RN6,RN7,RN8,RN9",R_Array_Convex_4x0603,C29718
BOOTSEL,SW1,SW_Push_1P1T_XKB_TS-1187A,C318884
RESET,SW2,SW_Push_1P1T_XKB_TS-1187A,C318884
RP2354A,U1,QFN-60-1EP_7x7mm_P0.4mm_EP3.4x3.4mm_ThermalVias,C41378174
AP2112K-3.3,U2,SOT-23-5,C51118
USBLC6-2SC6,U3,SOT-23-6,C7519
78L05,U4,SOT-89-3,C347258
TLP2361,"U5,U6,U7,U8,U9",Toshiba_SOIC-5-6_4.4x3.6mm_P1.27mm,C107626
74HCT165,"U10,U11,U12,U13,U14",SOIC-16_3.9x9.9mm_P1.27mm,C456131
74HC595,"U15,U16",SOIC-16_3.9x9.9mm_P1.27mm,C5947
12MHz,Y1,Crystal_SMD_3225-4Pin_3.2x2.5mm,C20625731
